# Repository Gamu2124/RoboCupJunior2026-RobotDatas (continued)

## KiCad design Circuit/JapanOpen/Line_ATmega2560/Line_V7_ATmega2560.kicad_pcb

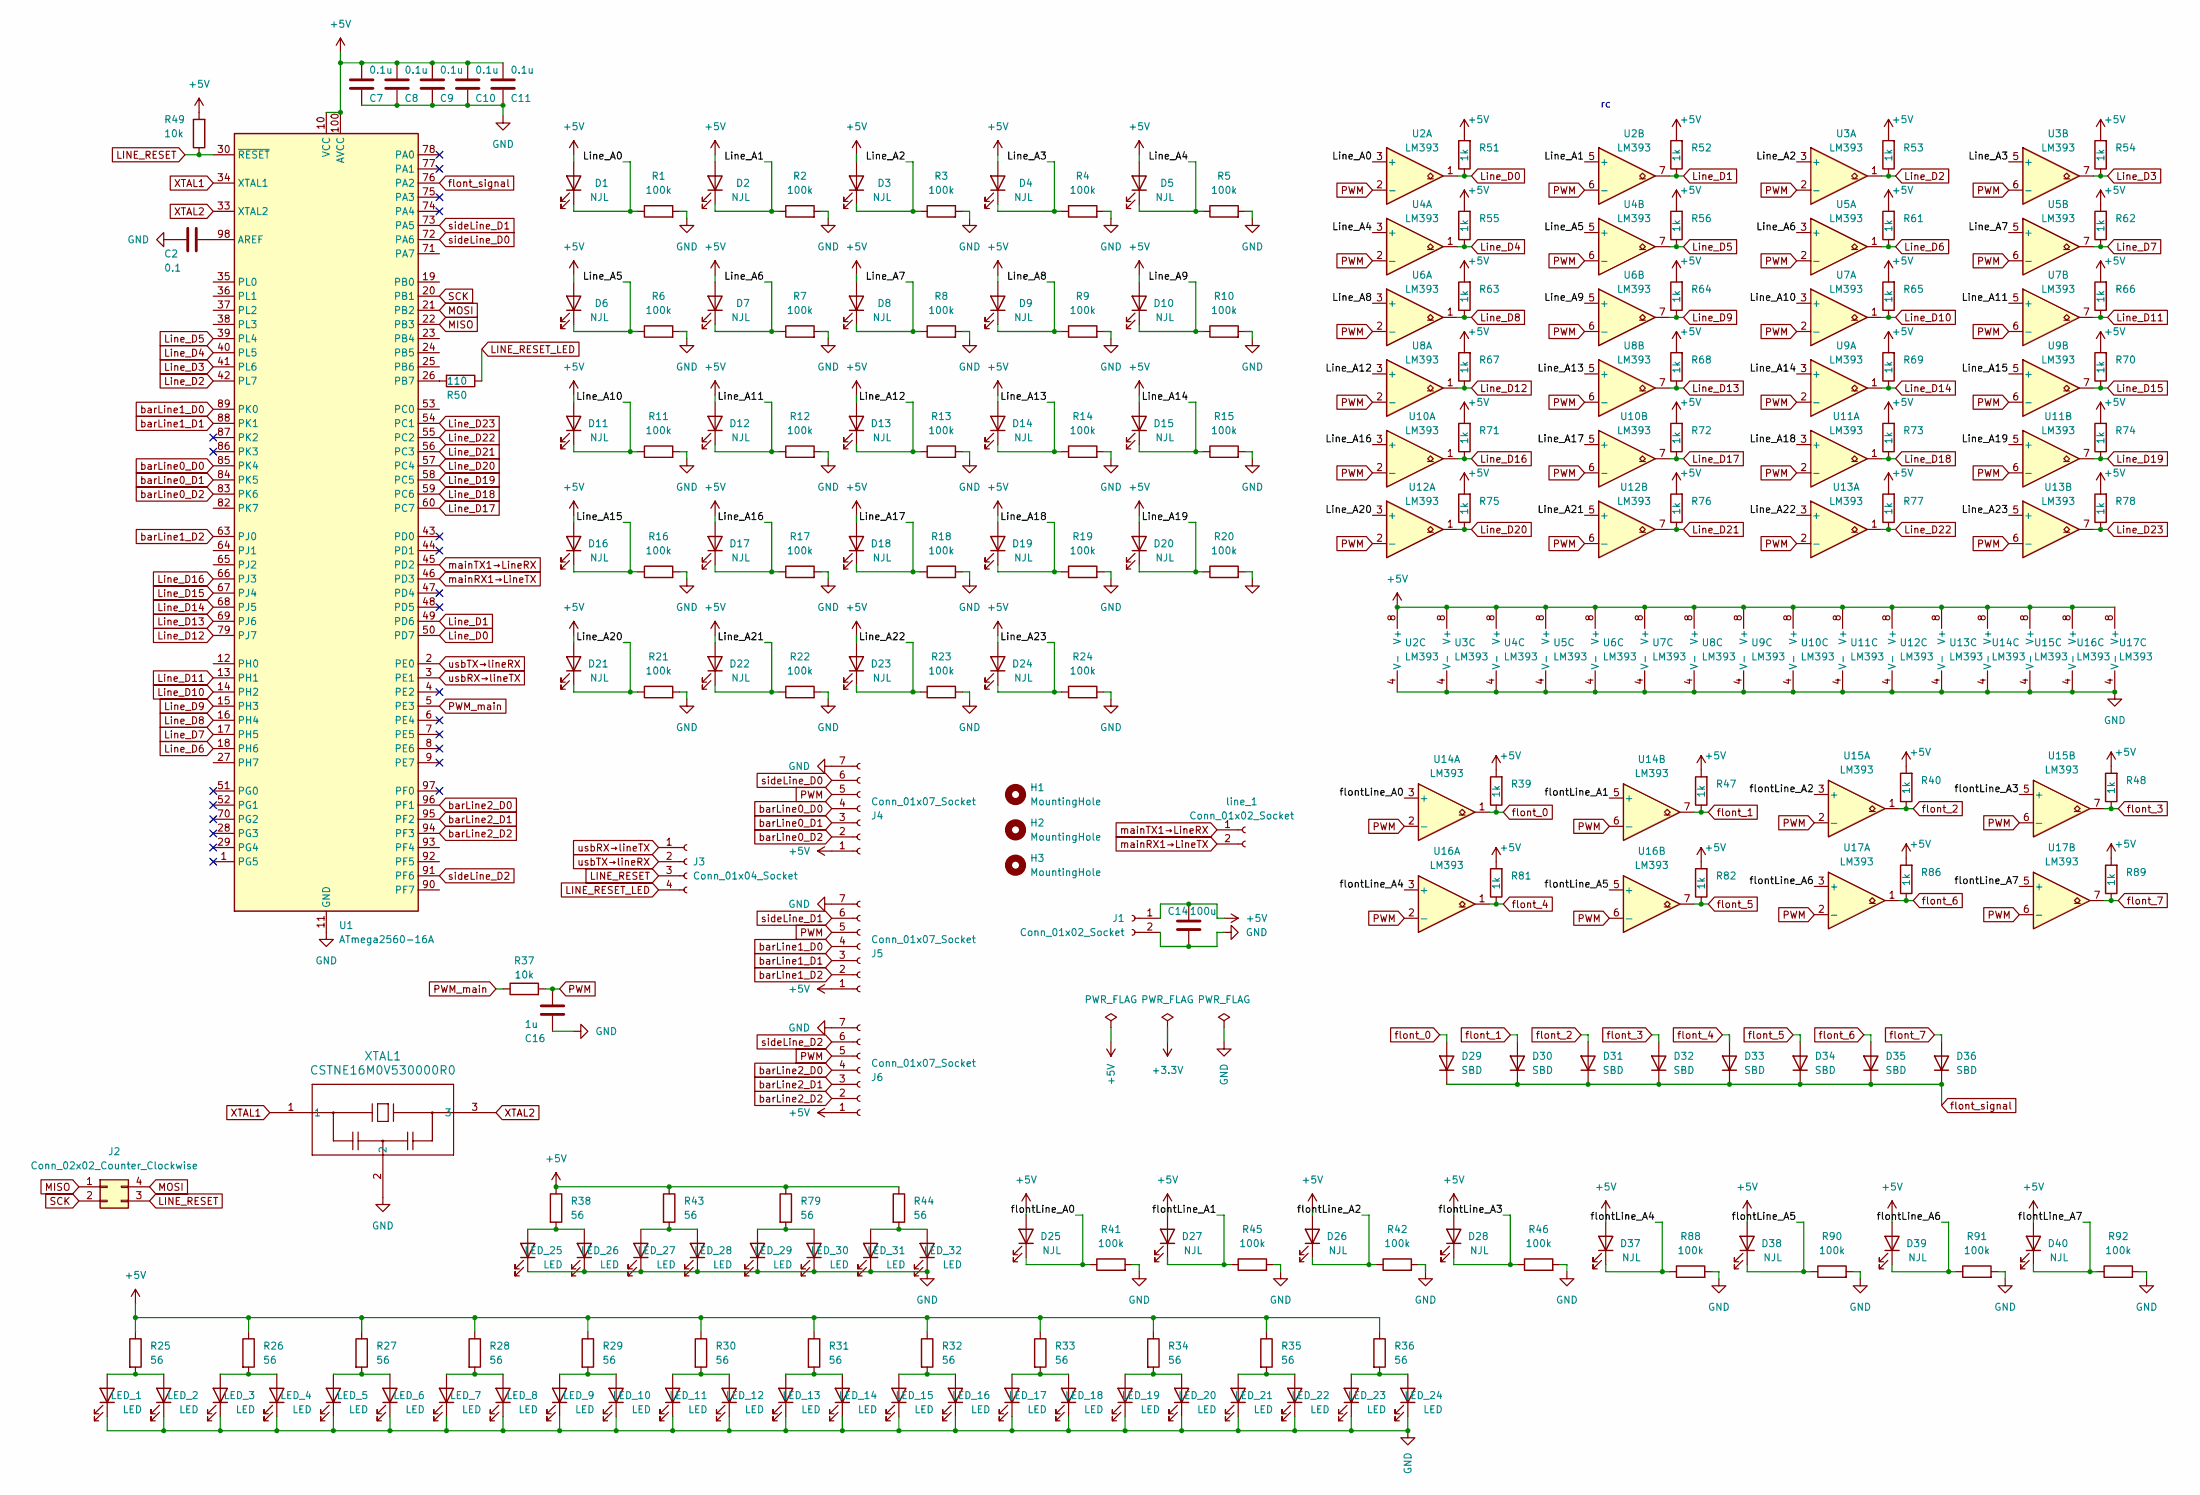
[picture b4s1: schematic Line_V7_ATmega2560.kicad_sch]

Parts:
C2: 0.1; C_0603_1608Metric_Pad1.08x0.95mm_HandSolder
C7, C8, C9, C10, C11: 0.1u; C_0603_1608Metric_Pad1.08x0.95mm_HandSolder; LCSC C1555
C14: 100u; C_Elec_5x5.4
C16: 1u; C_Elec_4x5.4; LCSC C3348
D1, D2, D3, D4, D5, D6, D7, D8, D9, D10, D11, D12, D13, D14, D15, D16, D17, D18, D19, D20, D21, D22, D23, D24, D25, D26, D27, D28, D37, D38, D39, D40: NJL; LED_0603_1608Metric
D29, D30, D31, D32, D33, D34, D35, D36: SBD; D_SOD-323
H1, H2, H3: MountingHole; MountingHole_3.2mm_M3
J1: Conn_01x02_Socket; JST_XH_S2B-XH-A-1_1x02_P2.50mm_Horizontal
J2: Conn_02x02_Counter_Clockwise; PinHeader_2x02_P2.54mm_Vertical
J3: Conn_01x04_Socket; JST_XH_S4B-XH-A_1x04_P2.50mm_Horizontal
J4, J5, J6: Conn_01x07_Socket; PinSocket_1x07_P2.54mm_Vertical
LED_1, LED_2, LED_3, LED_4, LED_5, LED_6, LED_7, LED_8, LED_9, LED_10, LED_11, LED_12, LED_13, LED_14, LED_15, LED_16, LED_17, LED_18, LED_19, LED_20, LED_21, LED_22, LED_23, LED_24, LED_25, LED_26, LED_27, LED_28, LED_29, LED_30, LED_31, LED_32: LED; LED_0603_1608Metric_Pad1.05x0.95mm_HandSolder
R1, R2, R3, R4, R5, R6, R7, R8, R9, R10, R11, R12, R13, R14, R15, R16, R17, R18, R19, R20, R21, R22, R23, R24, R41, R42, R45, R46, R88, R90, R91, R92: 100k; R_0603_1608Metric; LCSC C23098
R25, R26, R27, R28, R29, R30, R31, R32, R33, R34, R35, R36, R38, R43, R44, R79: 56; R_1206_3216Metric; LCSC C17995
R37, R49: 10k; R_0603_1608Metric; LCSC C23098
R39, R40, R47, R48, R51, R52, R53, R54, R55, R56, R61, R62, R63, R64, R65, R66, R67, R68, R69, R70, R71, R72, R73, R74, R75, R76, R77, R78, R81, R82, R86, R89: 1k; R_0603_1608Metric; LCSC C23098
R50: 110; R_1206_3216Metric; LCSC C17909
U1: ATmega2560-16A; TQFP-100_14x14mm_P0.5mm
U2, U3, U4, U5, U6, U7, U8, U9, U10, U11, U12, U13, U14, U15, U16, U17: LM393; SOIC-8_3.9x4.9mm_P1.27mm
XTAL1: CSTNE16M0V530000R0; CSTNE16M0V530000R0_MUR
line_1: Conn_01x02_Socket; JST_XH_S2B-XH-A-1_1x02_P2.50mm_Horizontal

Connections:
+5V: C7.2, C8.2, C9.2, C10.2, C11.2, C14.1, D1.2 (A), D2.2 (A), D3.2 (A), D4.2 (A), D5.2 (A), D6.2 (A), D7.2 (A), D8.2 (A), D9.2 (A), D10.2 (A), D11.2 (A), D12.2 (A), D13.2 (A), D14.2 (A), D15.2 (A), D16.2 (A), D17.2 (A), D18.2 (A), D19.2 (A), D20.2 (A), D21.2 (A), D22.2 (A), D23.2 (A), D24.2 (A), D25.2 (A), D26.2 (A), D27.2 (A), D28.2 (A), D37.2 (A), D38.2 (A), D39.2 (A), D40.2 (A), J1.1, J4.1, J5.1, J6.1, R25.1, R26.1, R27.1, R28.1, R29.1, R30.1, R31.1, R32.1, R33.1, R34.1, R35.1, R36.1, R38.1, R39.2, R40.2, R43.1, R44.1, R47.2, R48.2, R49.2, R51.2, R52.2, R53.2, R54.2, R55.2, R56.2, R61.2, R62.2, R63.2, R64.2, R65.2, R66.2, R67.2, R68.2, R69.2, R70.2, R71.2, R72.2, R73.2, R74.2, R75.2, R76.2, R77.2, R78.2, R79.1, R81.2, R82.2, R86.2, R89.2, U1.10 (VCC), U1.31 (VCC), U1.61 (VCC), U1.80 (VCC), U1.100 (AVCC), U2.8 (V+), U3.8 (V+), U4.8 (V+), U5.8 (V+), U6.8 (V+), U7.8 (V+), U8.8 (V+), U9.8 (V+), U10.8 (V+), U11.8 (V+), U12.8 (V+), U13.8 (V+), U14.8 (V+), U15.8 (V+), U16.8 (V+), U17.8 (V+); also elsewhere on the board
/Line_A0: D1.1 (K), R1.1, U2.3 (+)
/Line_A1: D2.1 (K), R2.1, U2.5 (+)
/Line_A2: D3.1 (K), R3.1, U3.3 (+)
/Line_A3: D4.1 (K), R4.1, U3.5 (+)
/Line_A4: D5.1 (K), R5.1, U4.3 (+)
/Line_A5: D6.1 (K), R6.1, U4.5 (+)
/Line_A6: D7.1 (K), R7.1, U5.3 (+)
/Line_A7: D8.1 (K), R8.1, U5.5 (+)
/Line_A8: D9.1 (K), R9.1, U6.3 (+)
/Line_A9: D10.1 (K), R10.1, U6.5 (+)
/Line_A10: D11.1 (K), R11.1, U7.3 (+)
/Line_A11: D12.1 (K), R12.1, U7.5 (+)
/Line_A12: D13.1 (K), R13.1, U8.3 (+)
/Line_A13: D14.1 (K), R14.1, U8.5 (+)
/Line_A14: D15.1 (K), R15.1, U9.3 (+)
/Line_A15: D16.1 (K), R16.1, U9.5 (+)
/Line_A16: D17.1 (K), R17.1, U10.3 (+)
/Line_A17: D18.1 (K), R18.1, U10.5 (+)
/Line_A18: D19.1 (K), R19.1, U11.3 (+)
/Line_A19: D20.1 (K), R20.1, U11.5 (+)
/Line_A20: D21.1 (K), R21.1, U12.3 (+)
/Line_A21: D22.1 (K), R22.1, U12.5 (+)
/Line_A22: D23.1 (K), R23.1, U13.3 (+)
/Line_A23: D24.1 (K), R24.1, U13.5 (+)
/flontLine_A0: D25.1 (K), R41.1, U14.3 (+)
/flontLine_A1: D27.1 (K), R45.1, U14.5 (+)
/flontLine_A2: D26.1 (K), R42.1, U15.3 (+)
/flontLine_A3: D28.1 (K), R46.1, U15.5 (+)
/flontLine_A4: D37.1 (K), R88.1, U16.3 (+)
/flontLine_A5: D38.1 (K), R90.1, U16.5 (+)
/flontLine_A6: D39.1 (K), R91.1, U17.3 (+)
/flontLine_A7: D40.1 (K), R92.1, U17.5 (+)
GND: C2.2, C7.1, C8.1, C9.1, C10.1, C11.1, C14.2, C16.2, J1.2, J4.7, J5.7, J6.7, LED_1.1 (K), LED_2.1 (K), LED_3.1 (K), LED_4.1 (K), LED_5.1 (K), LED_6.1 (K), LED_7.1 (K), LED_8.1 (K), LED_9.1 (K), LED_10.1 (K), LED_11.1 (K), LED_12.1 (K), LED_13.1 (K), LED_14.1 (K), LED_15.1 (K), LED_16.1 (K), LED_17.1 (K), LED_18.1 (K), LED_19.1 (K), LED_20.1 (K), LED_21.1 (K), LED_22.1 (K), LED_23.1 (K), LED_24.1 (K), LED_25.1 (K), LED_26.1 (K), LED_27.1 (K), LED_28.1 (K), LED_29.1 (K), LED_30.1 (K), LED_31.1 (K), LED_32.1 (K), R1.2, R2.2, R3.2, R4.2, R5.2, R6.2, R7.2, R8.2, R9.2, R10.2, R11.2, R12.2, R13.2, R14.2, R15.2, R16.2, R17.2, R18.2, R19.2, R20.2, R21.2, R22.2, R23.2, R24.2, R41.2, R42.2, R45.2, R46.2, R88.2, R90.2, R91.2, R92.2, U1.11 (GND), U1.32 (GND), U1.62 (GND), U1.81 (GND), U1.99 (GND), U2.4 (V-), U3.4 (V-), U4.4 (V-), U5.4 (V-), U6.4 (V-), U7.4 (V-), U8.4 (V-), U9.4 (V-), U10.4 (V-), U11.4 (V-), U12.4 (V-), U13.4 (V-), U14.4 (V-), U15.4 (V-), U16.4 (V-), U17.4 (V-), XTAL1.2
LINE_RESET: J2.3, J3.3, R49.1, U1.30 (~RESET)
LINE_RESET_LED: J3.4, R50.1
Line_D0: R51.1, U1.50 (PD7), U2.1
Line_D1: R52.1, U1.49 (PD6), U2.7
Line_D2: R53.1, U1.42 (PL7), U3.1
Line_D3: R54.1, U1.41 (PL6), U3.7
Line_D4: R55.1, U1.40 (PL5), U4.1
Line_D5: R56.1, U1.39 (PL4), U4.7
Line_D6: R61.1, U1.18 (PH6), U5.1
Line_D7: R62.1, U1.17 (PH5), U5.7
Line_D8: R63.1, U1.16 (PH4), U6.1
Line_D9: R64.1, U1.15 (PH3), U6.7
Line_D10: R65.1, U1.14 (PH2), U7.1
Line_D11: R66.1, U1.13 (PH1), U7.7
Line_D12: R67.1, U1.79 (PJ7), U8.1
Line_D13: R68.1, U1.69 (PJ6), U8.7
Line_D14: R69.1, U1.68 (PJ5), U9.1
Line_D15: R70.1, U1.67 (PJ4), U9.7
Line_D16: R71.1, U1.66 (PJ3), U10.1
Line_D17: R72.1, U1.60 (PC7), U10.7
Line_D18: R73.1, U1.59 (PC6), U11.1
Line_D19: R74.1, U1.58 (PC5), U11.7
Line_D20: R75.1, U1.57 (PC4), U12.1
Line_D21: R76.1, U1.56 (PC3), U12.7
Line_D22: R77.1, U1.55 (PC2), U13.1
Line_D23: R78.1, U1.54 (PC1), U13.7
MISO: J2.1, U1.22 (PB3)
MOSI: J2.4, U1.21 (PB2)
unnamed: LED_1.2 (A), LED_2.2 (A), R25.2
unnamed: LED_3.2 (A), LED_4.2 (A), R26.2
unnamed: LED_5.2 (A), LED_6.2 (A), R27.2
unnamed: LED_7.2 (A), LED_8.2 (A), R28.2
unnamed: LED_9.2 (A), LED_10.2 (A), R29.2
unnamed: LED_11.2 (A), LED_12.2 (A), R30.2
unnamed: LED_13.2 (A), LED_14.2 (A), R31.2
unnamed: LED_15.2 (A), LED_16.2 (A), R32.2
unnamed: LED_17.2 (A), LED_18.2 (A), R33.2
unnamed: LED_19.2 (A), LED_20.2 (A), R34.2
unnamed: LED_21.2 (A), LED_22.2 (A), R35.2
unnamed: LED_23.2 (A), LED_24.2 (A), R36.2
unnamed: LED_25.2 (A), LED_26.2 (A), R38.2
unnamed: LED_27.2 (A), LED_28.2 (A), R43.2
unnamed: LED_29.2 (A), LED_30.2 (A), R79.2
unnamed: LED_31.2 (A), LED_32.2 (A), R44.2
unnamed: C2.1, U1.98 (AREF)
unnamed: R50.2, U1.26 (PB7)
PWM: C16.1, J4.5, J5.5, J6.5, R37.2, U2.2 (-), U2.6 (-), U3.2 (-), U3.6 (-), U4.2 (-), U4.6 (-), U5.2 (-), U5.6 (-), U6.2 (-), U6.6 (-), U7.2 (-), U7.6 (-), U8.2 (-), U8.6 (-), U9.2 (-), U9.6 (-), U10.2 (-), U10.6 (-), U11.2 (-), U11.6 (-), U12.2 (-), U12.6 (-), U13.2 (-), U13.6 (-), U14.2 (-), U14.6 (-), U15.2 (-), U15.6 (-), U16.2 (-), U16.6 (-), U17.2 (-), U17.6 (-)
PWM_main: R37.1, U1.5 (PE3)
SCK: J2.2, U1.20 (PB1)
XTAL1: U1.34 (XTAL1), XTAL1.1
XTAL2: U1.33 (XTAL2), XTAL1.3
barLine0_D0: J4.4, U1.85 (PK4)
barLine0_D1: J4.3, U1.84 (PK5)
barLine0_D2: J4.2, U1.83 (PK6)
barLine1_D0: J5.4, U1.89 (PK0)
barLine1_D1: J5.3, U1.88 (PK1)
barLine1_D2: J5.2, U1.63 (PJ0)
barLine2_D0: J6.4, U1.96 (PF1)
barLine2_D1: J6.3, U1.95 (PF2)
barLine2_D2: J6.2, U1.94 (PF3)
flont_0: D29.2 (A), R39.1, U14.1
flont_1: D30.2 (A), R47.1, U14.7; also elsewhere on the board
flont_2: D31.2 (A), R40.1, U15.1; also elsewhere on the board
flont_3: D32.2 (A), R48.1, U15.7; also elsewhere on the board
flont_4: D33.2 (A), R81.1, U16.1; also elsewhere on the board
flont_5: D34.2 (A), R82.1, U16.7; also elsewhere on the board
flont_6: D35.2 (A), R86.1, U17.1
flont_7: D36.2 (A), R89.1, U17.7
flont_signal: D29.1 (K), D30.1 (K), D31.1 (K), D32.1 (K), D33.1 (K), D34.1 (K), D35.1 (K), D36.1 (K), U1.76 (PA2)
mainRX1→LineTX: U1.46 (PD3), line_1.2
mainTX1→LineRX: U1.45 (PD2), line_1.1
sideLine_D0: J4.6, U1.72 (PA6)
sideLine_D1: J5.6, U1.73 (PA5)
sideLine_D2: J6.6, U1.91 (PF6)
usbRX→lineTX: J3.1, U1.3 (PE1)
usbTX→lineRX: J3.2, U1.2 (PE0)

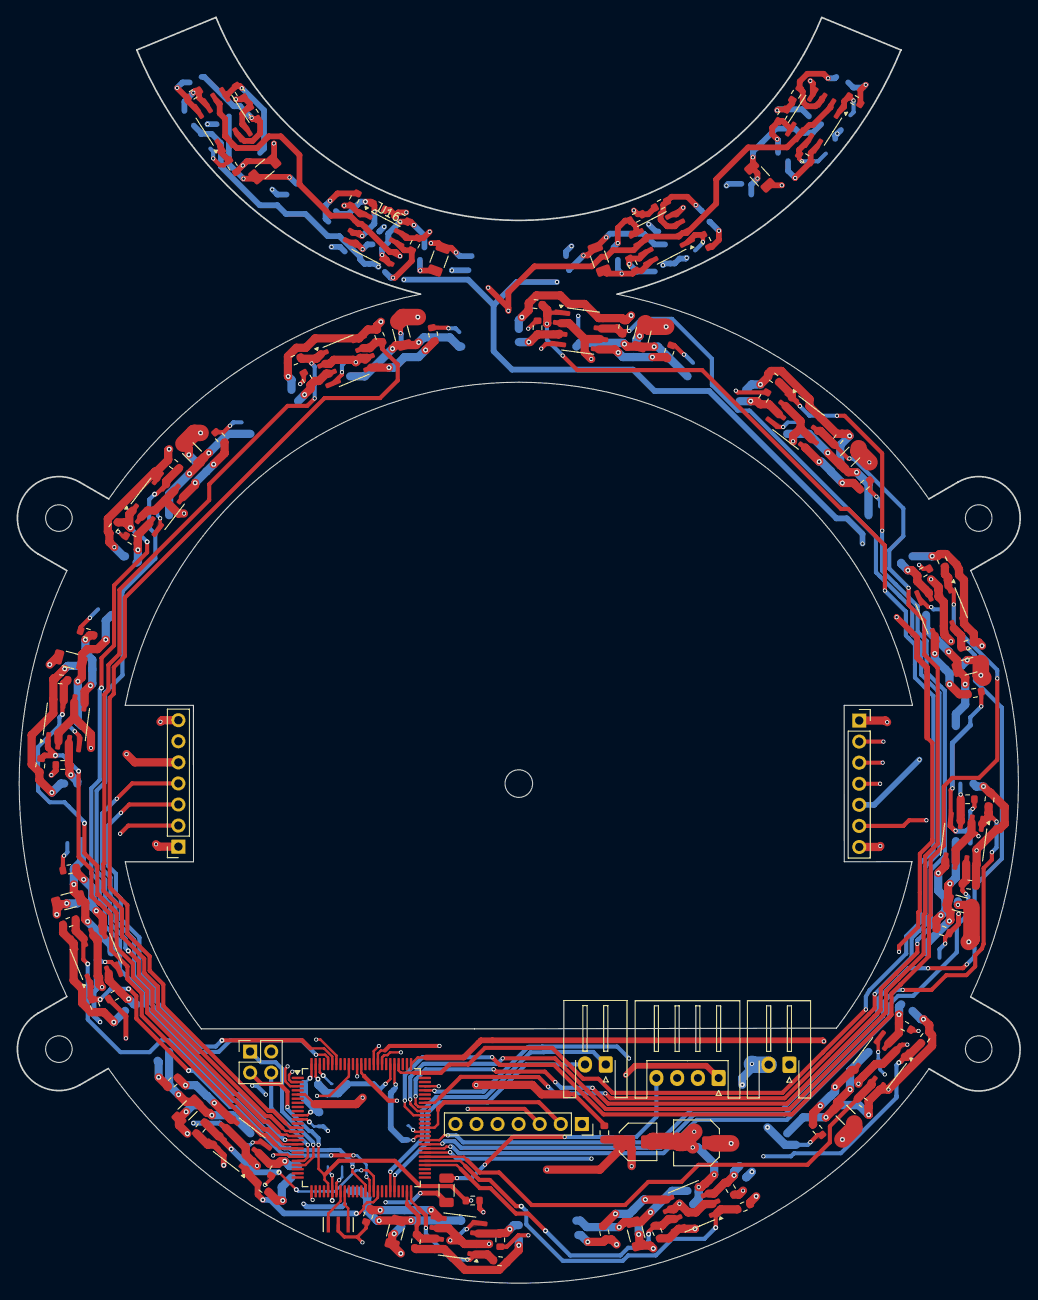
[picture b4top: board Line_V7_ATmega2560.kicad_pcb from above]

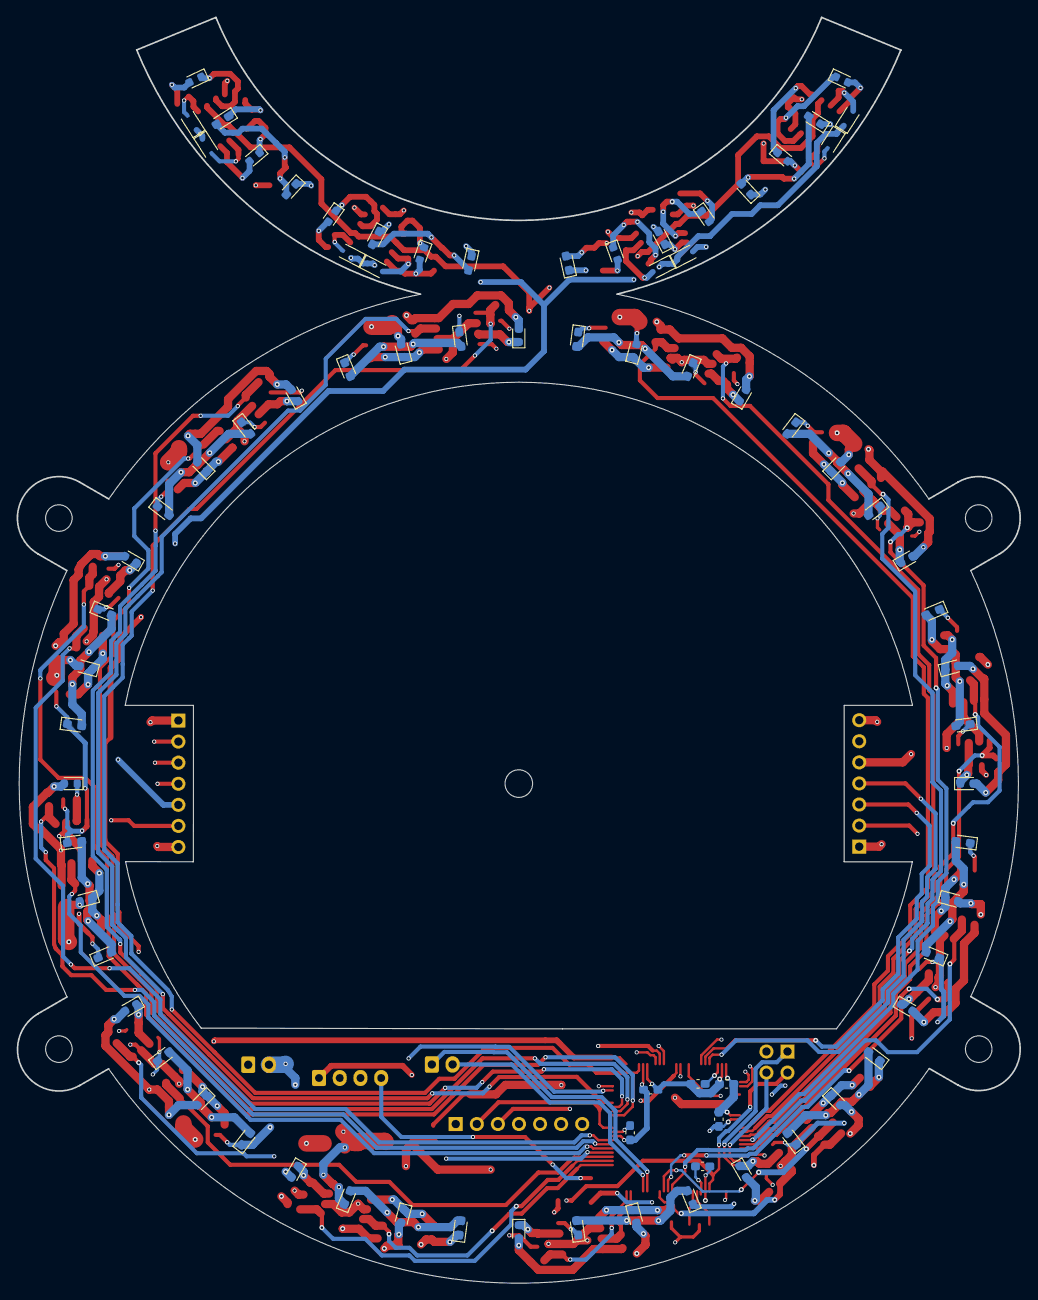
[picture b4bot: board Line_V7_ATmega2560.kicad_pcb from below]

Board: 4 copper layers, 120.8 x 152.5 mm, 188 parts (78 on the bottom side), 110 nets.

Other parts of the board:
R58, R59, R60, R83, R84: 1k; R_0603_1608Metric

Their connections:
+5V: R58.2, R59.2, R60.2, R83.2, R84.2; also elsewhere on the board
flont_1: R58.1; also elsewhere on the board
flont_2: R59.1; also elsewhere on the board
flont_3: R60.1; also elsewhere on the board
flont_4: R83.1; also elsewhere on the board
flont_5: R84.1; also elsewhere on the board

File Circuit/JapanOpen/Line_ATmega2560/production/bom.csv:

Designator,Footprint,Quantity,Value,LCSC Part #
"C10, C11, C7, C8, C9",0603,5,0.1u,C1555
C14,C_Elec_5x5.4,1,100u,
C16,C_Elec_4x5.4,1,1u,C3348
C2,0603,1,0.1,
"D1, D10, D11, D12, D13, D14, D15, D16, D17, D18, D19, D2, D20, D21, D22, D23, D24, D25, D26, D27, D28, D3, D37, D38, D39, D4, D40, D5, D6, D7, D8, D9",0603,32,NJL,
"D29, D30, D31, D32, D33, D34, D35, D36",D_SOD-323,8,SBD,
"J1, LINE_1",JST_XH_S2B-XH-A-1_1x02_P2.50mm_Horizontal,2,Conn_01x02_Socket,
J2,PinHeader_2x02_P2.54mm_Vertical,1,Conn_02x02_Counter_Clockwise,
J3,JST_XH_S4B-XH-A_1x04_P2.50mm_Horizontal,1,Conn_01x04_Socket,
"J4, J5, J6",PinSocket_1x07_P2.54mm_Vertical,3,Conn_01x07_Socket,
"LED_1, LED_10, LED_11, LED_12, LED_13, LED_14, LED_15, LED_16, LED_17, LED_18, LED_19, LED_2, LED_20, LED_21, LED_22, LED_23, LED_24, LED_25, LED_26, LED_27, LED_28, LED_29, LED_3, LED_30, LED_31, LED_32, LED_4, LED_5, LED_6, LED_7, LED_8, LED_9",0603,32,LED,
"R1, R10, R11, R12, R13, R14, R15, R16, R17, R18, R19, R2, R20, R21, R22, R23, R24, R3, R4, R41, R42, R45, R46, R5, R6, R7, R8, R88, R9, R90, R91, R92",0603,32,100k,C23098
"R25, R26, R27, R28, R29, R30, R31, R32, R33, R34, R35, R36, R38, R43, R44, R79",1206,16,56,C17995
"R37, R49",0603,2,10k,C23098
"R39, R51, R52, R53, R54, R55, R56, R58, R59, R60, R61, R62, R63, R64, R65, R66, R67, R68, R69, R70, R71, R72, R73, R74, R75, R76, R77, R78, R83, R84, R86, R89",0603,32,1k,C23098
R50,1206,1,110,C17909
U1,TQFP-100_14x14mm_P0.5mm,1,ATmega2560-16A,
"U10, U11, U12, U13, U14, U15, U16, U17, U2, U3, U4, U5, U6, U7, U8, U9",SOIC-8_3.9x4.9mm_P1.27mm,16,LM393,
XTAL1,CSTNE16M0V530000R0_MUR,1,CSTNE16M0V530000R0,

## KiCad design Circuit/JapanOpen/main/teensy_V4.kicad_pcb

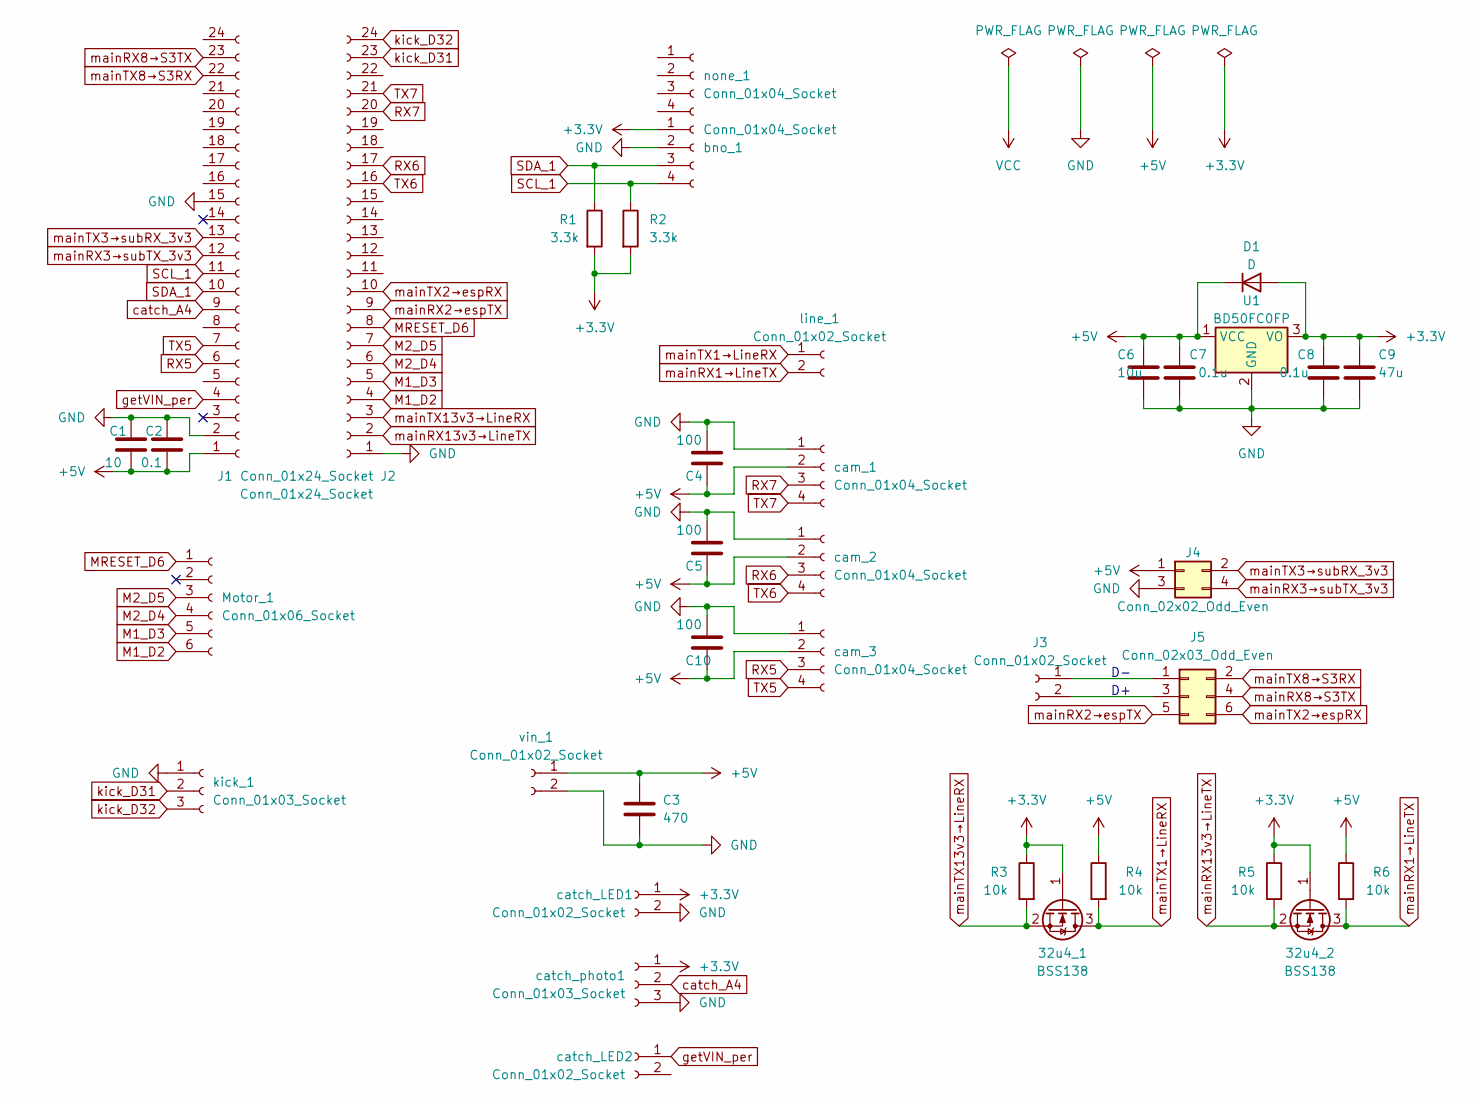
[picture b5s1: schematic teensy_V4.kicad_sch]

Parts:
32u4_1, 32u4_2: BSS138; SOT-23; LCSC C192057
C1: 10; C_Disc_D5.1mm_W3.2mm_P5.00mm
C2: 0.1; C_Disc_D5.0mm_W2.5mm_P2.50mm
C3: 470; C_Radial_D12.5mm_H20.0mm_P5.00mm
C4, C5, C10: 100; CP_Radial_D5.0mm_P2.00mm
C6: 10u; C_Disc_D5.1mm_W3.2mm_P5.00mm; LCSC C1713
C7, C8: 0.1u; C_Disc_D5.0mm_W2.5mm_P2.50mm; LCSC C1581
C9: 47u; CP_Radial_D5.0mm_P2.00mm; LCSC C3337
D1: D; D_SOD-123F
J1, J2: Conn_01x24_Socket; PinSocket_1x24_P2.54mm_Vertical
J3: Conn_01x02_Socket; PinSocket_1x02_P2.54mm_Vertical
J4: Conn_02x02_Odd_Even; PinHeader_2x02_P2.54mm_Vertical
J5: Conn_02x03_Odd_Even; PinSocket_2x03_P2.54mm_Vertical
Motor_1: Conn_01x06_Socket; TE_84952-6_1x06-1MP_P1.0mm_Horizontal
R1: 3.3k; R_Axial_DIN0207_L6.3mm_D2.5mm_P10.16mm_Horizontal
R2: 3.3k; R_Axial_DIN0207_L6.3mm_D2.5mm_P10.16mm_Horizontal; LCSC C22978
R3, R4, R5, R6: 10k; R_1206_3216Metric_Pad1.30x1.75mm_HandSolder; LCSC C1489
U1: BD50FC0FP; TO-252-2
bno_1: Conn_01x04_Socket; PinSocket_1x04_P2.54mm_Vertical
cam_1, cam_2, cam_3: Conn_01x04_Socket; JST_XH_B4B-XH-A_1x04_P2.50mm_Vertical
catch_LED1, catch_LED2: Conn_01x02_Socket; JST_XH_B2B-XH-A_1x02_P2.50mm_Vertical
catch_photo1: Conn_01x03_Socket; JST_XH_B3B-XH-A_1x03_P2.50mm_Vertical
kick_1: Conn_01x03_Socket; JST_XH_B3B-XH-A_1x03_P2.50mm_Vertical
line_1: Conn_01x02_Socket; JST_XH_B2B-XH-A_1x02_P2.50mm_Vertical
none_1: Conn_01x04_Socket; PinSocket_1x04_P2.54mm_Vertical
vin_1: Conn_01x02_Socket; JST_XH_B2B-XH-A_1x02_P2.50mm_Vertical

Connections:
+3.3V: 32u4_1.1 (G), 32u4_2.1 (G), C8.1, C9.1, D1.2 (A), R1.2, R2.2, R3.1, R5.1, U1.3 (VO), bno_1.1, catch_LED1.1, catch_photo1.1
+5V: C1.2, C2.2, C3.1, C4.1, C5.1, C6.1, C7.1, C10.1, D1.1 (K), J1.1, J4.1, R4.1, R6.1, U1.1 (VCC), cam_1.2, cam_2.2, cam_3.2, vin_1.1
GND: C1.1, C2.1, C3.2, C4.2, C5.2, C6.2, C7.2, C8.2, C9.2, C10.2, J1.2, J1.15, J2.1, J4.3, U1.2 (GND), bno_1.2, cam_1.1, cam_2.1, cam_3.1, catch_LED1.2, catch_photo1.3, kick_1.1, vin_1.2
M1_D2: J2.4, Motor_1.6
M1_D3: J2.5, Motor_1.5
M2_D4: J2.6, Motor_1.4
M2_D5: J2.7, Motor_1.3
MRESET_D6: J2.8, Motor_1.1
unnamed: J3.1, J5.1
unnamed: J3.2, J5.3
RX5: J1.6, cam_3.3
RX6: J2.17, cam_2.3
RX7: J2.20, cam_1.3
SCL_1: J1.11, R2.1, bno_1.4
SDA_1: J1.10, R1.1, bno_1.3
TX5: J1.7, cam_3.4
TX6: J2.16, cam_2.4
TX7: J2.21, cam_1.4
catch_A4: J1.9, catch_photo1.2
getVIN_per: J1.4, catch_LED2.1
kick_D31: J2.23, kick_1.2
kick_D32: J2.24, kick_1.3
mainRX1→LineTX: 32u4_2.3 (D), R6.2, line_1.2
mainRX2→espTX: J2.9, J5.5
mainRX3→subTX_3v3: J1.12, J4.4
mainRX8→S3TX: J1.23, J5.4
mainRX13v3→LineTX: 32u4_2.2 (S), J2.2, R5.2
mainTX1→LineRX: 32u4_1.3 (D), R4.2, line_1.1
mainTX2→espRX: J2.10, J5.6
mainTX3→subRX_3v3: J1.13, J4.2
mainTX8→S3RX: J1.22, J5.2
mainTX13v3→LineRX: 32u4_1.2 (S), J2.3, R3.2

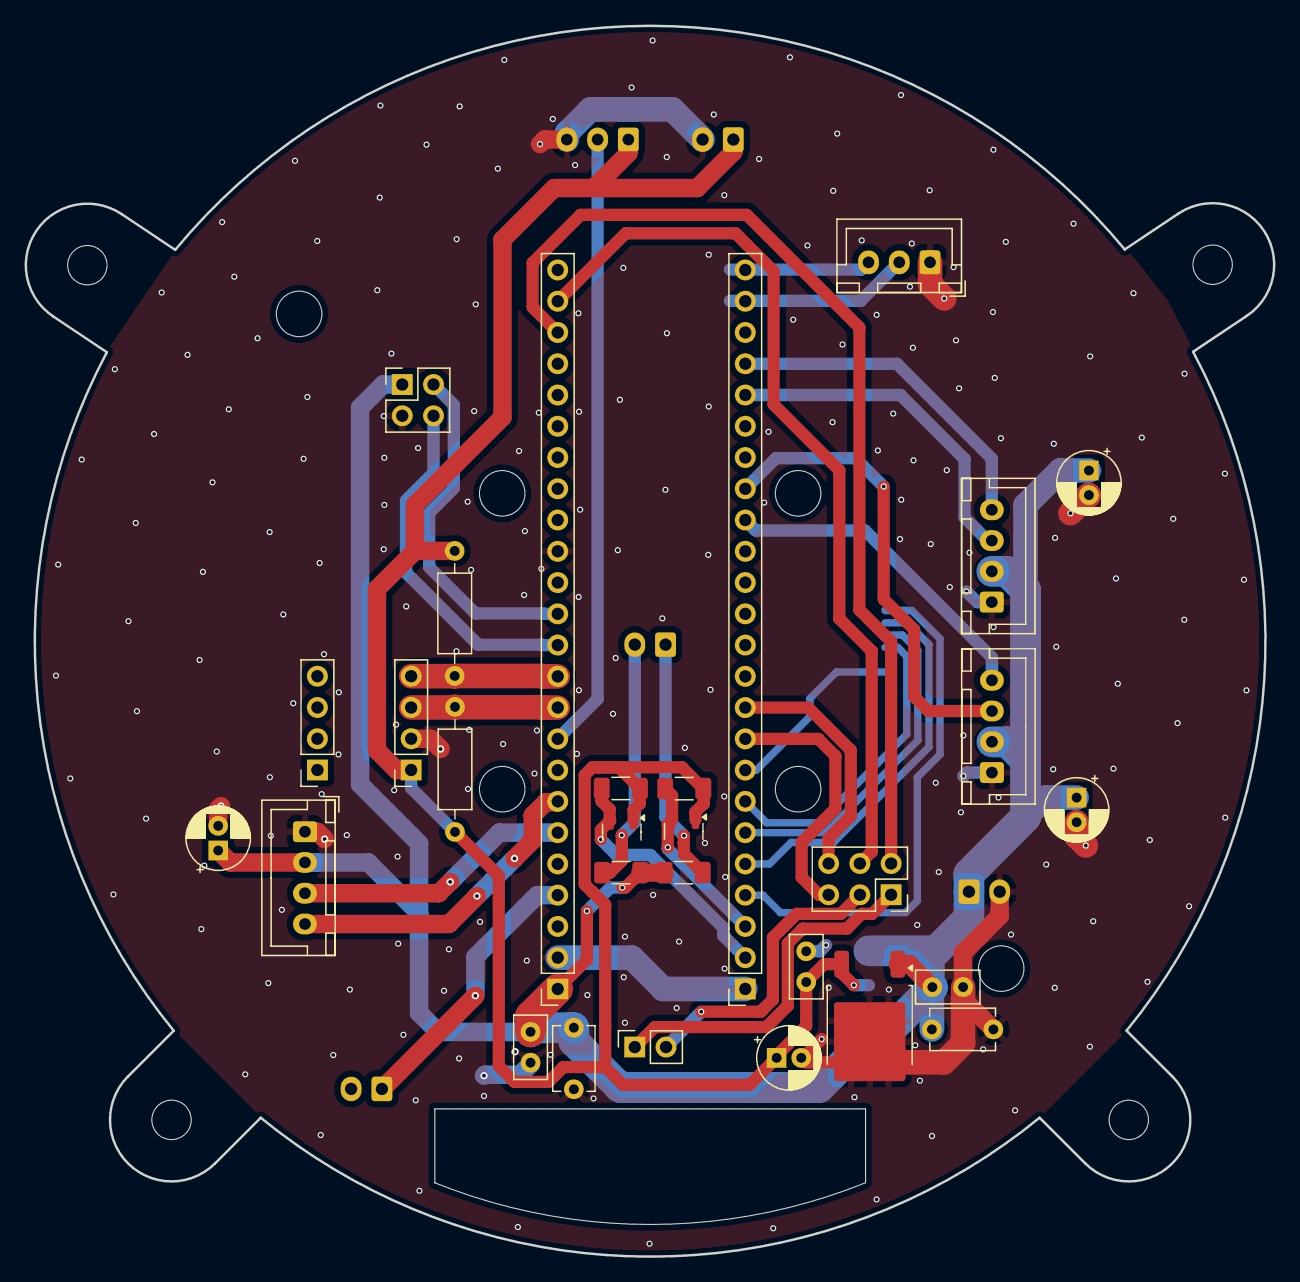
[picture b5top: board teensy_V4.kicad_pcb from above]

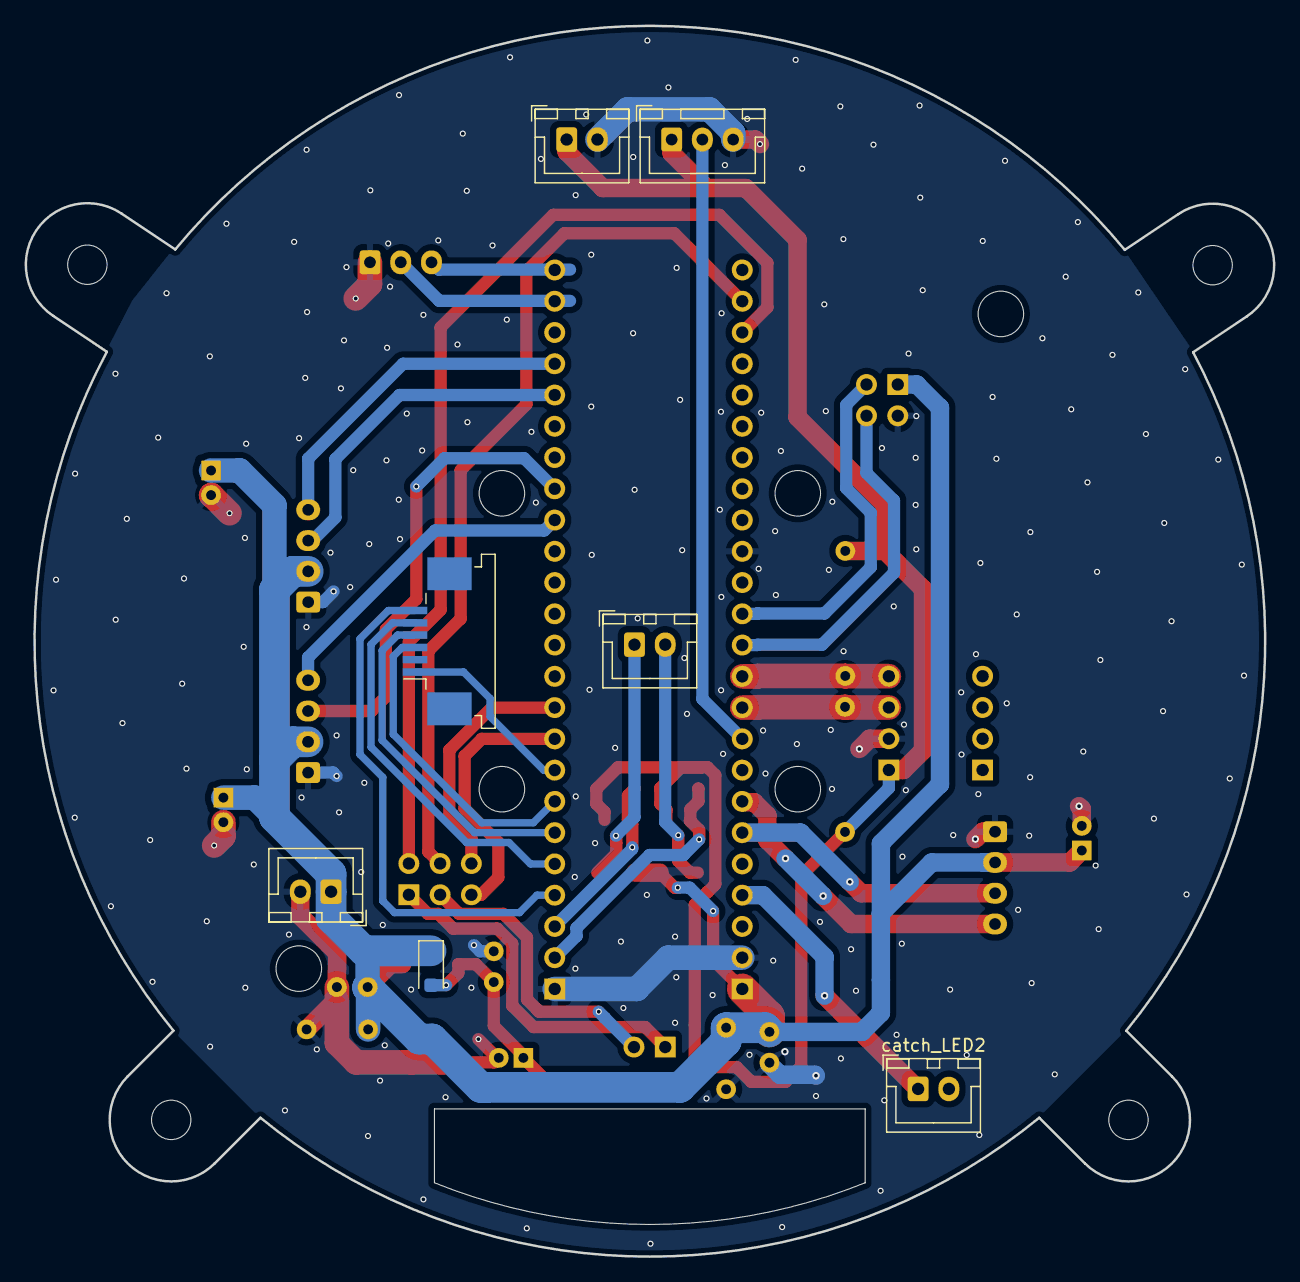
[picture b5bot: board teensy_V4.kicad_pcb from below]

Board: 2 copper layers, 101.4 x 100.0 mm, 40 parts (7 on the bottom side), 32 nets.

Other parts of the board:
H1, H2, H3, H4: MountingHole; MountingHole_3.2mm_M3

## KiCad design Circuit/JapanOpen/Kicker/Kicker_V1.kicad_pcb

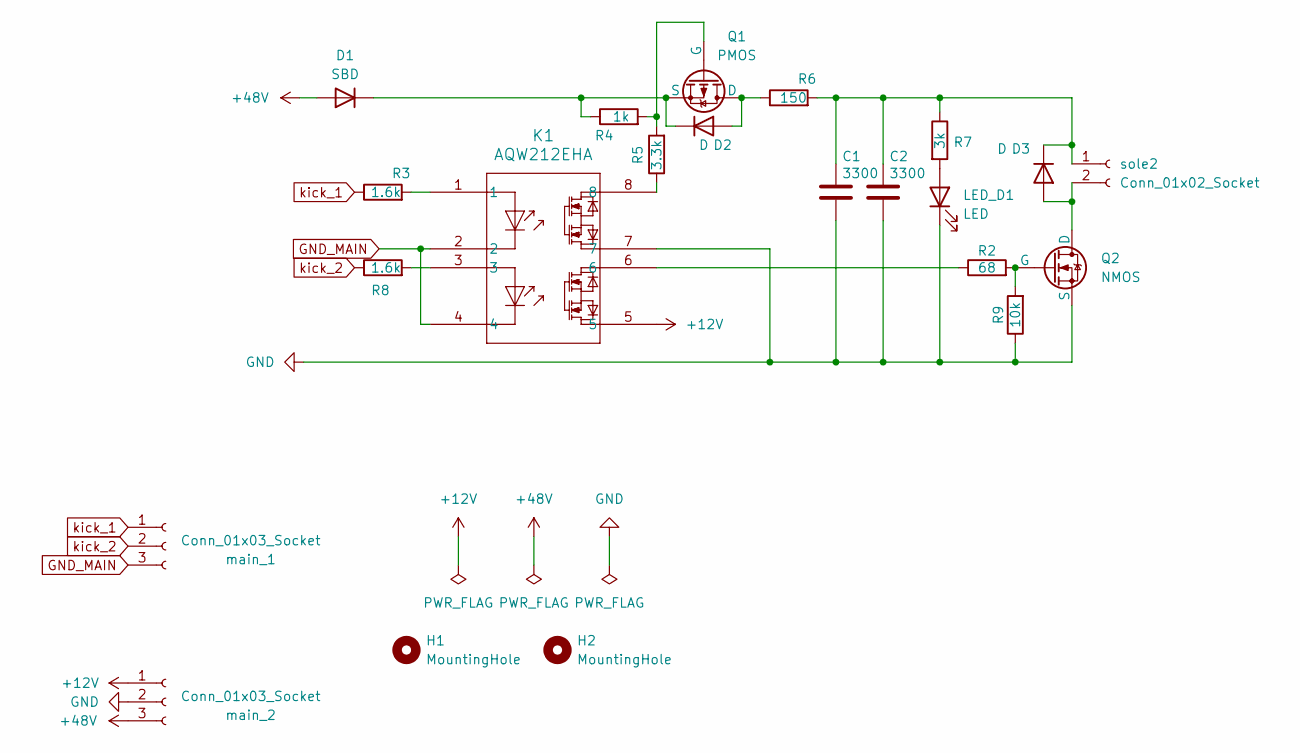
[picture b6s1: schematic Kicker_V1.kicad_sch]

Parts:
C1, C2: 3300; C_Radial_D18.0mm_H35.5mm_P7.50mm
D1: SBD; D_SOD-323_HandSoldering
D2, D3: D; D_SOD-123F
H1, H2: MountingHole; MountingHole_3.2mm_M3
K1: AQW212EHA; SMDIP-8_W7.62mm
LED_D1: LED; LED_0603_1608Metric_Pad1.05x0.95mm_HandSolder
Q1: PMOS; TO-252-2
Q2: NMOS; TO-220-3_Horizontal_TabDown
R2: 68; R_1206_3216Metric
R3: 1.6k; R_1206_3216Metric; LCSC C4908
R4: 1k; R_2512_6332Metric; LCSC C31884
R5: 3.3k; R_2512_6332Metric; LCSC C1469
R6: 150; R_2512_6332Metric; LCSC C25471
R7: 3k; R_2512_6332Metric; LCSC C2934109
R8: 1.6k; R_1206_3216Metric; LCSC C102100
R9: 10k; R_1206_3216Metric
main_1, main_2: Conn_01x03_Socket; JST_XH_B3B-XH-A_1x03_P2.50mm_Vertical
sole2: Conn_01x02_Socket; JST_XH_B2B-XH-A_1x02_P2.50mm_Vertical

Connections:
+12V: K1.5, main_2.1
+48V: D1.2 (A), main_2.3
GND: C1.2, C2.2, K1.7, LED_D1.1 (K), Q2.3 (S), R9.1, main_2.2
GND_MAIN: K1.2, K1.4, main_1.3
unnamed: D1.1 (K), D2.1 (K), Q1.3 (S), R4.1
unnamed: D2.2 (A), Q1.2 (D), R6.1
unnamed: D3.2 (A), Q2.1 (D), sole2.2
unnamed: C1.1, C2.1, D3.1 (K), R6.2, R7.1, sole2.1
unnamed: K1.1, R3.2
unnamed: K1.3, R8.2
unnamed: K1.6, R2.1
unnamed: K1.8, R5.1
unnamed: LED_D1.2 (A), R7.2
unnamed: Q1.1 (G), R4.2, R5.2
unnamed: Q2.2 (G), R2.2, R9.2
kick_1: R3.1, main_1.1
kick_2: R8.1, main_1.2

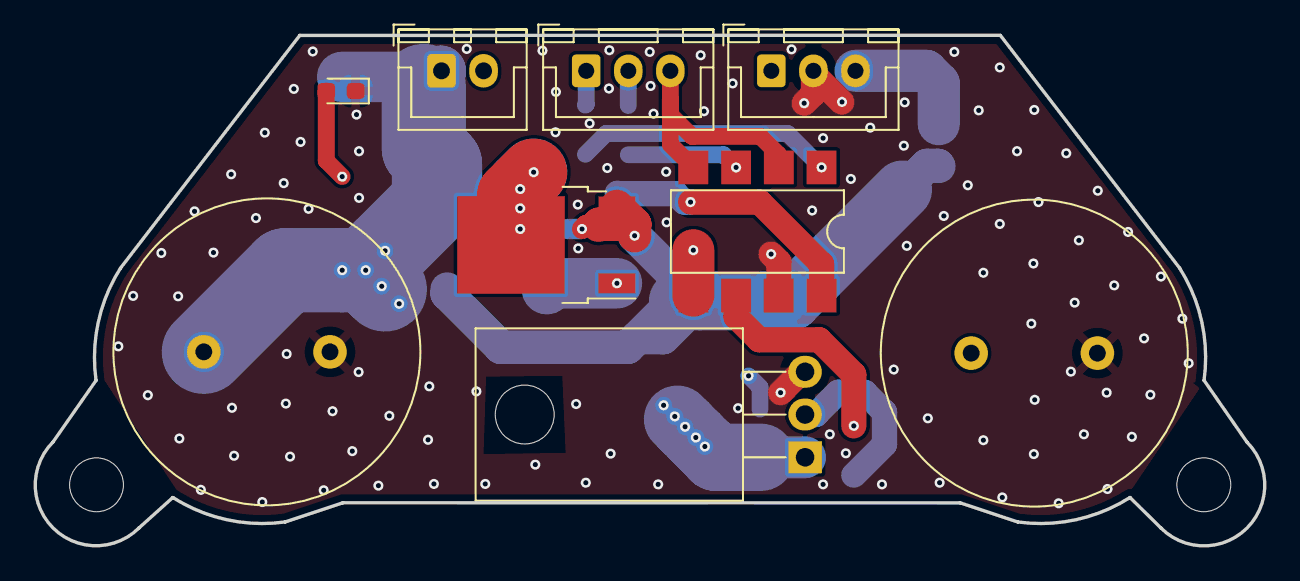
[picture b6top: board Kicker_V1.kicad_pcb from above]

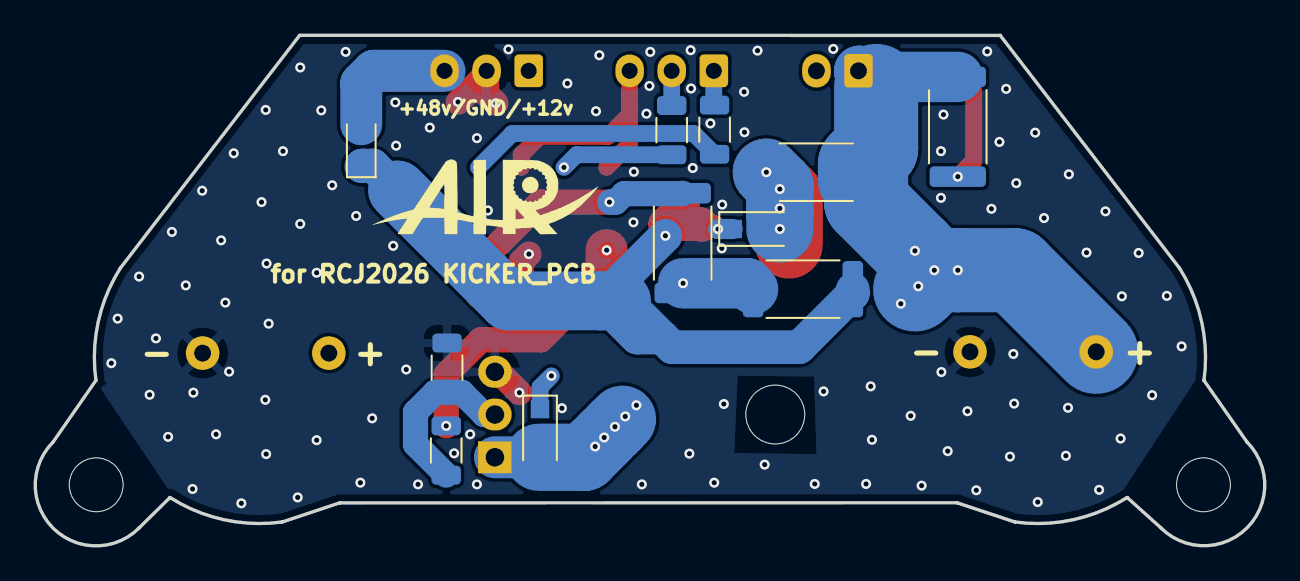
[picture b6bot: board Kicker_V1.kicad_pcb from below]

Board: 4 copper layers, 73.1 x 30.3 mm, 22 parts (11 on the bottom side), 17 nets.

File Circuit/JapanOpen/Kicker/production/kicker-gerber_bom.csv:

Designator,Footprint,Quantity,Value,LCSC Part #
"C1, C2",C_Radial_D18.0mm_H35.5mm_P7.50mm,2,3300,
D1,D_SOD-323_HandSoldering,1,SBD,
"D2, D3",D_SOD-123F,2,D,
K1,SMDIP-8_W7.62mm,1,AQW212EHA,
LED_D1,0603,1,LED,
"MAIN_1, MAIN_2",JST_XH_B3B-XH-A_1x03_P2.50mm_Vertical,2,Conn_01x03_Socket,
Q1,TO-252-2,1,PMOS,
Q2,TO-220-3_Horizontal_TabDown,1,NMOS,
R2,1206,1,68,
R3,1206,1,1.6k,C4908
R4,2512,1,1k,C31884
R5,2512,1,3.3k,C1469
R6,2512,1,150,C25471
R7,2512,1,3k,C2934109
R8,1206,1,1.6k,C102100 
R9,1206,1,10k,
SOLE2,JST_XH_B2B-XH-A_1x02_P2.50mm_Vertical,1,Conn_01x02_Socket,
